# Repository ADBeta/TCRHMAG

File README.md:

# Temperature Controlled Ryobi Hot Melt Adhesive Gun

An Upgrade Control Board for the R18GLU Hot Glue Gun to provide PID Temperature
Control, and display battery voltage, battery current.  
It also improves battery life to 1hr 45min on a 1.5Ah Ryobi Battery (At 150c).

## Features
This is a drop-in replacement Controller PCB, which provides:

* OLED Display which shows
    * Target and Actual Temperature
    * Battery Current draw
    * Battery Voltage (and Battery Bar)
* Overcurrent and Undervoltage Protection
* Adjustable PID Control loop
* LED Status Light
* Precise Temperature Control (+/-5 degrees celcius)

## How do I install this mod?
This upgrade will require ordering PCBs & components, soldering, modifying the
chassis, and barrel of the Glue Gun as well as 3D Printing.  
TCRHMAG is a medium difficulty hobby project.

1) Remove the Original Controller board and remove the wires from the Power Switch
2) **MODIFICATION STEPS**  
2a) Drill a small hole in the Glue Gun's heater barrel for better thermal control,
and use a thermally rated (280c) adhesive to attach an NTC Thermistor (TODO: images and specs of thermistor)
2b) Create a notch in both halves of the Glue Gun Shell for the OLED and Control wires (TODO: Images)
using a Dremel or sharp knife etc.
2c) (TODO: add display control 3d printed housing)
3) Install the programmed PCB
4) Solder the Power Switch to the PCB, and solder the Thermistor, Heater, LED
and Battery cables to the PCB
5) **3D PRINTED OLED HOUSING STEPS**
5a)......

## Programming The Microcontorller
**IMPORTANT** Solder and Flash the MCU **BEFORE** Assembling the rest of the PCB  
The NRST Line is used by an OpAmp circuit so it CANNOT be flashed in-situ until
the NRST line is disabled by the first Flash Cycle.
After this initial Programming Step, the board can be fully assembled and 
re-programmed if necessary without removing parts.

Use [minichlink](https://github.com/cnlohr/ch32fun/tree/master/minichlink) to
program the MCU.  
This project is built using [ch32fun](https://github.com/cnlohr/ch32fun).

## Bill of Materials

## To Do
* Display in Faranheit?
* Add better Rotary Encoder filter circuit
* Fix noisy battery voltage sensing
* Larget OLED / Rotary Encoder solder pads

----
Copyright (c) 2026 ADBeta

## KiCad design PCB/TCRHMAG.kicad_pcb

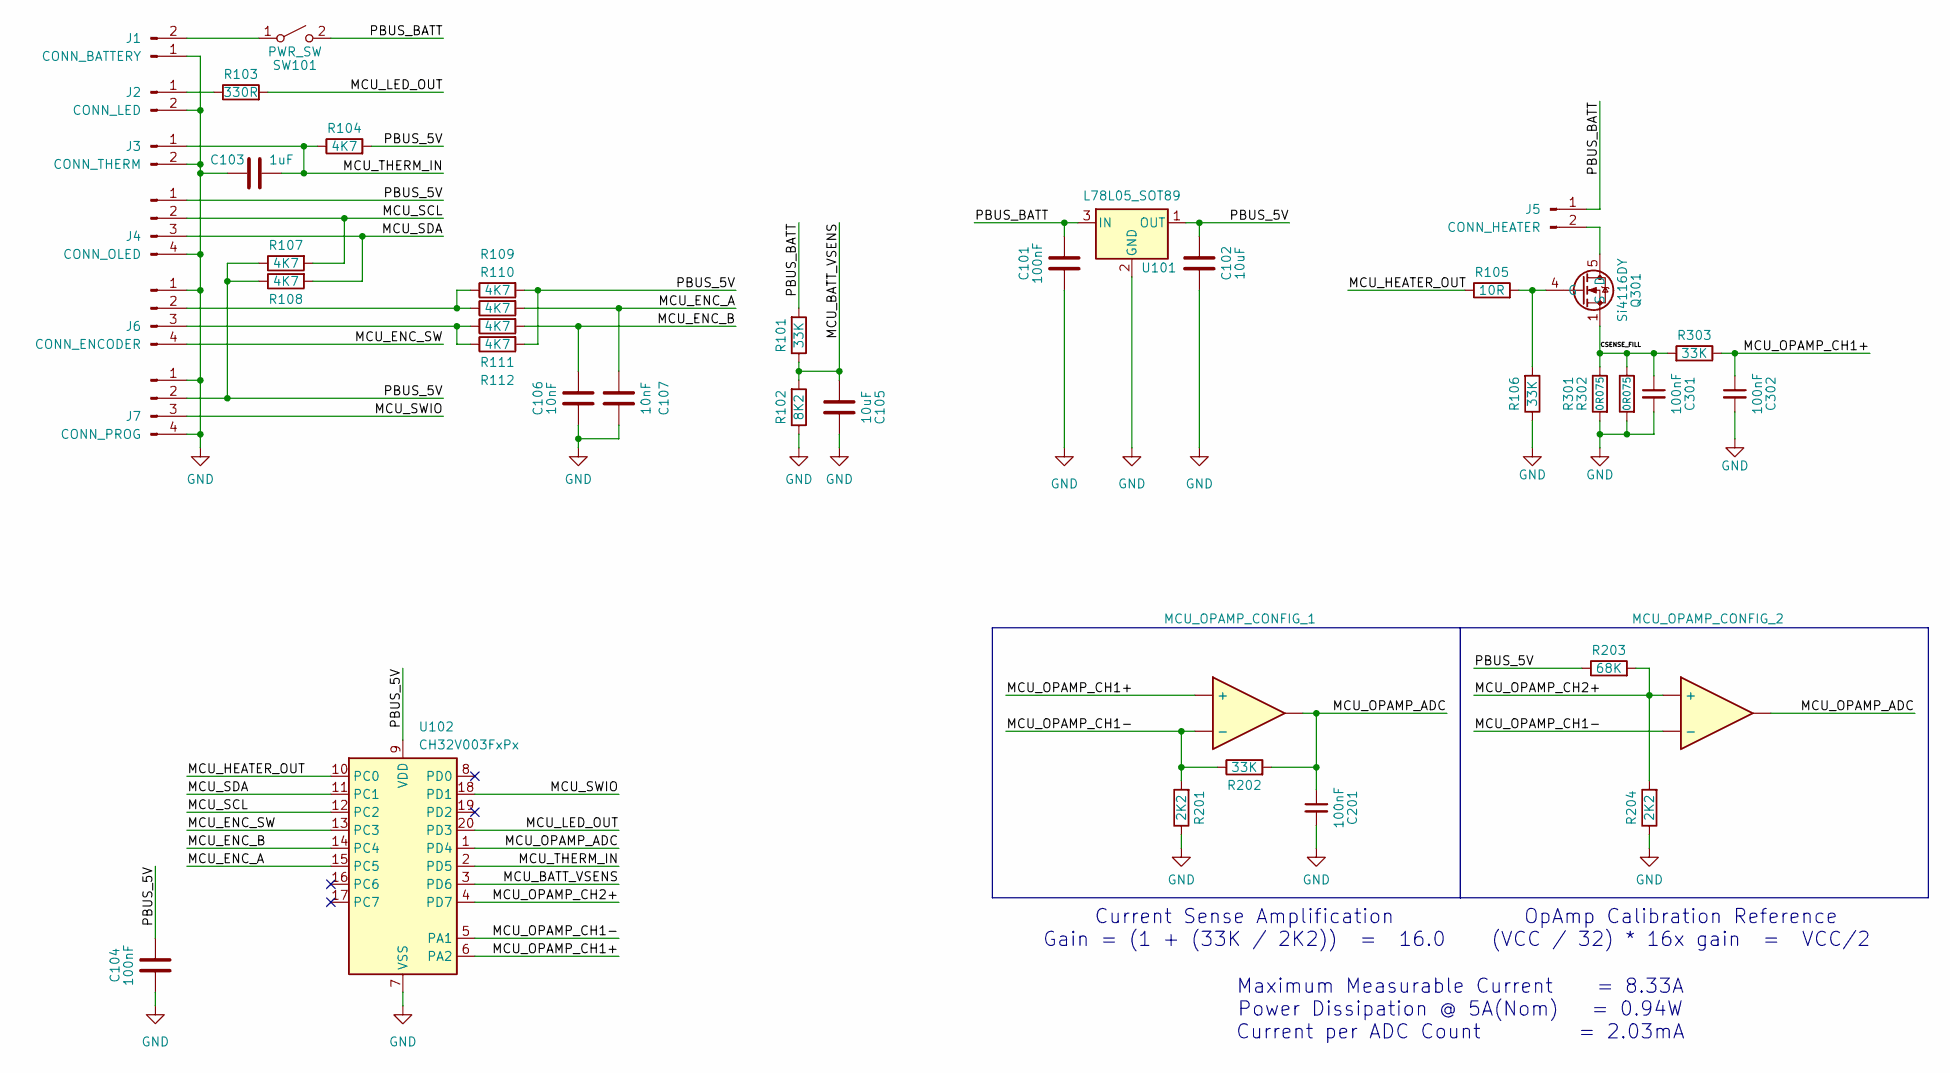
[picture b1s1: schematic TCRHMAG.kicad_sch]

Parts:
C101, C104, C201, C301, C302: 100nF; C_0402_1005Metric
C102, C105: 10uF; C_0402_1005Metric
C103: 1uF; C_0402_1005Metric
C106, C107: 10nF; C_0402_1005Metric
J1: CONN_BATTERY; Power_Conn
J2: CONN_LED; Signal_Conn
J3: CONN_THERM; Signal_Conn
J4: CONN_OLED; PinSocket_1x04_P2.00mm_Vertical
J5: CONN_HEATER; Power_Conn
J6: CONN_ENCODER; PinSocket_1x04_P2.00mm_Vertical
J7: CONN_PROG; Program_Conn
MCU_OPAMP_CONFIG_1, MCU_OPAMP_CONFIG_2: (no value)
Q301: Si4116DY; SOIC-8_3.9x4.9mm_P1.27mm
R101, R106, R202, R303: 33K; R_0402_1005Metric
R102: 8K2; R_0402_1005Metric
R103: 330R; R_0402_1005Metric
R104, R107, R108, R109, R110, R111, R112: 4K7; R_0402_1005Metric
R105: 10R; R_0402_1005Metric
R201, R204: 2K2; R_0402_1005Metric
R203: 68K; R_0402_1005Metric
R301, R302: 0R075; R_2512_6332Metric_Pad1.40x3.35mm_HandSolder
SW101: PWR_SW; U13SS_Switch
U101: L78L05_SOT89; SOT-89-3
U102: CH32V003FxPx; TSSOP-20_4.4x6.5mm_P0.65mm

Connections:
/CSENSE_FILL: C301.1, Q301.1 (S), Q301.2 (S), Q301.3 (S), R301.1, R302.1, R303.2
/MCU_BATT_VSENS: C105.1, R101.1, R102.2, U102.3 (PD6)
/MCU_ENC_A: C107.2, R110.2, U102.15 (PC5)
/MCU_ENC_B: C106.2, R111.2, U102.14 (PC4)
/MCU_ENC_SW: J6.4, U102.13 (PC3)
/MCU_HEATER_OUT: R105.1, U102.10 (PC0)
/MCU_LED_OUT: R103.2, U102.20 (PD3)
/MCU_OPAMP_ADC: C201.1, MCU_OPAMP_CONFIG_1.3, MCU_OPAMP_CONFIG_2.3, R202.2, U102.1 (PD4)
/MCU_OPAMP_CH1+: C302.1, MCU_OPAMP_CONFIG_1.1 (+), R303.1, U102.6 (PA2)
/MCU_OPAMP_CH1-: MCU_OPAMP_CONFIG_1.2 (-), MCU_OPAMP_CONFIG_2.2 (-), R201.2, R202.1, U102.5 (PA1)
/MCU_OPAMP_CH2+: MCU_OPAMP_CONFIG_2.1 (+), R203.2, R204.2, U102.4 (PD7)
/MCU_SCL: J4.2, R107.2, U102.12 (PC2)
/MCU_SDA: J4.3, R108.2, U102.11 (PC1)
/MCU_SWIO: J7.3, U102.18 (PD1)
/MCU_THERM_IN: C103.2, J3.1, R104.1, U102.2 (PD5)
/PBUS_5V: C102.1, C104.1, J4.1, J7.2, R104.2, R107.1, R108.1, R109.2, R112.2, R203.1, U101.1 (OUT), U102.9 (VDD)
/PBUS_BATT: C101.1, J5.1, R101.2, SW101.2 (B), U101.3 (IN)
GND: C101.2, C102.2, C103.1, C104.2, C105.2, C106.1, C107.1, C201.2, C301.2, C302.2, J1.1, J2.2, J3.2, J4.4, J6.1, J7.1, J7.4, R102.1, R106.1, R201.1, R204.1, R301.2, R302.2, U101.2 (GND), U102.7 (VSS)
unnamed: J1.2, SW101.1 (A)
unnamed: J2.1, R103.1
unnamed: J5.2, Q301.5 (D), Q301.6 (D), Q301.7 (D), Q301.8 (D)
unnamed: J6.2, R109.1, R110.1
unnamed: J6.3, R111.1, R112.1
unnamed: Q301.4 (G), R105.2, R106.2

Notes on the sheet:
OpAmp Calibration Reference (VCC / 32) * 16x gain = VCC/2
Current Sense Amplification Gain = (1 + (33K / 2K2)) = 16.0
Maximum Measurable Current = 8.33A Power Dissipation @ 5A(Nom) = 0.94W Current per ADC Count = 2.03mA

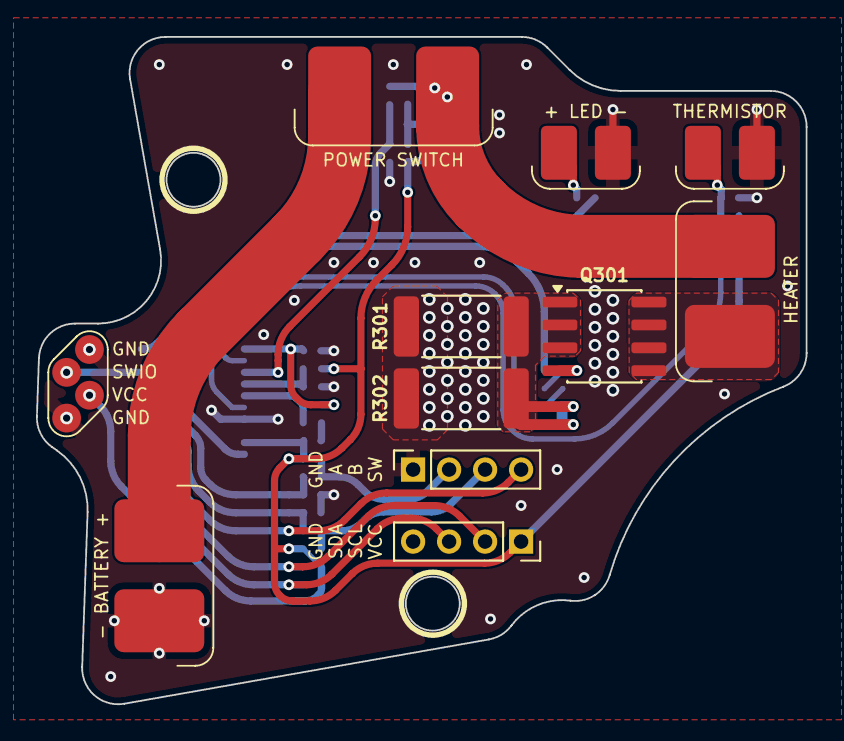
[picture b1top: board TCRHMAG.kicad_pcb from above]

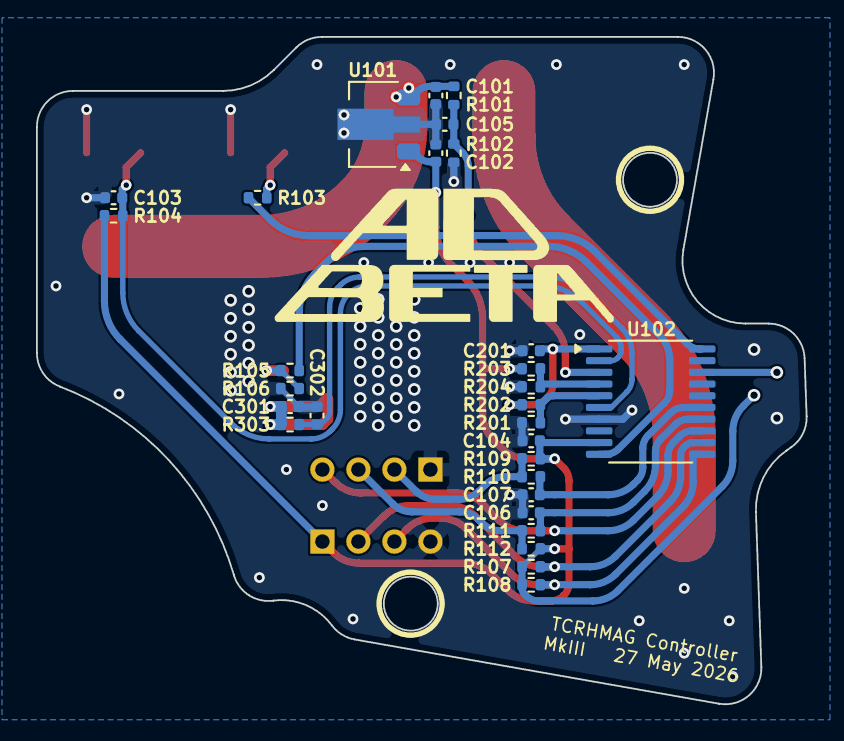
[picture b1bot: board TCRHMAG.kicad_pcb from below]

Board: 2 copper layers, 42.8 x 37.1 mm, 40 parts (29 on the bottom side), 24 nets.

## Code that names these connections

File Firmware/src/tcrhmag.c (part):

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*
*
* ---- Pinout ----
* PA1    OPAMP_CH1-
* PA2    OPAMP_CH1+
*
* PC0    PWM Out           (TIM2 CH3)
* PC1    I2C SDA
* PC2    I2C_SCL
* PC3    Rotary Encoder Switch
* PC4    Rotary Encoder A
* PC5    Rotary Encoder B
*
* PD3    LED Out           (TIM2 CH2)
* PD4    OPAMP_ADC         (ADC7)
* PD5    Thermistor ADC    (ADC5)
* PD6    Battery Sense     (ADC6)
* PD7    OPAMP_CH2+
*
* ---- TODO ----
* - Scheduler Library
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

/*** Pin Definitions *********************************************************/
#define OPAMP_CHA1_NEG                GPIO_PA1
#define OPAMP_CHA1_POS                GPIO_PA2
#define OPAMP_CHA2_POS                GPIO_PD7
#define PWM_OUT                       GPIO_PC0

#define ROTENC_SW_PIN                 GPIO_PC3
#define ROTENC_A_PIN                  GPIO_PC4
#define ROTENC_B_PIN                  GPIO_PC5

#define THERM_ADC_PIN                 GPIO_A5
#define THERM_ADC_CH                  GPIO_ADC_A5
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		// Accumulate transitions per detend (usually 4) 
		static int8_t accumulator     = 0;
		
		// Read A and B Pins (PC4 & PC5), use their state as bits in a bitmask. [AB]
		static int8_t rotenc_prev_bitmask = 0b11;
		       int8_t rotenc_curr_bitmask = (((portc_read >> 4) & 1) << 1) | ((portc_read >> 5) & 1);

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
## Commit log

2026-01-09 LUT Generator Created
2026-01-15 PCB Started
2026-01-17 PCB Components Chosen
2026-01-20 Board Shape and Pad Placements
2026-01-23 Thermistor updates
2026-01-24 Added Current Sense to circuit
2026-01-26 Added High Current and MCU to PCB
2026-01-26 Started Firmware
2026-01-26 Adjusted LUT Python and header
2026-01-28 Started CH32V003 Integration
2026-02-07 Added OpAmp GPIO and init functions
2026-02-10 Firmware Testing
2026-03-06 Added temperature Linear Interpolation
2026-03-07 PID Control loop testing
2026-03-09 PID Heater control tested and tuned
2026-03-10 Final PCB
2026-03-12 Rotary Encoder and OpAmp Current Reading improvements
2026-03-14 Rotary Encoder to IRQ
2026-03-19 Fixed SWIO Bug. MkII HW
2026-03-19 I2C And OLED Testing
2026-03-20 OLED Working, begin font work
2026-05-04 OLED Framebuffer testing
2026-05-05 OLED Draw somewhat working
2026-05-06 Revising oled handler functions for battery status
2026-05-08 Refactored OLED draw routines and added battery percent icons
2026-05-15 Added large 16x16 font and string draw routine for it
2026-05-16 V1.0 Initial working MVP
2026-05-18 V1.1 added Bootscreen and fixed bug
2026-05-18 V1.2 Lockout mode added
2026-05-19 V1.3 Added heater indictor and Error state LED flashing
2026-05-20 V1.4 Improve failsafe mode
2026-05-25 MkIII PCB Finished
2026-05-27 PCB MkIII Final version gerber output. Changed gitignore
2026-05-29 Started overhaul
2026-05-30 V1.8 Created Scheduler library and converted code to use it
